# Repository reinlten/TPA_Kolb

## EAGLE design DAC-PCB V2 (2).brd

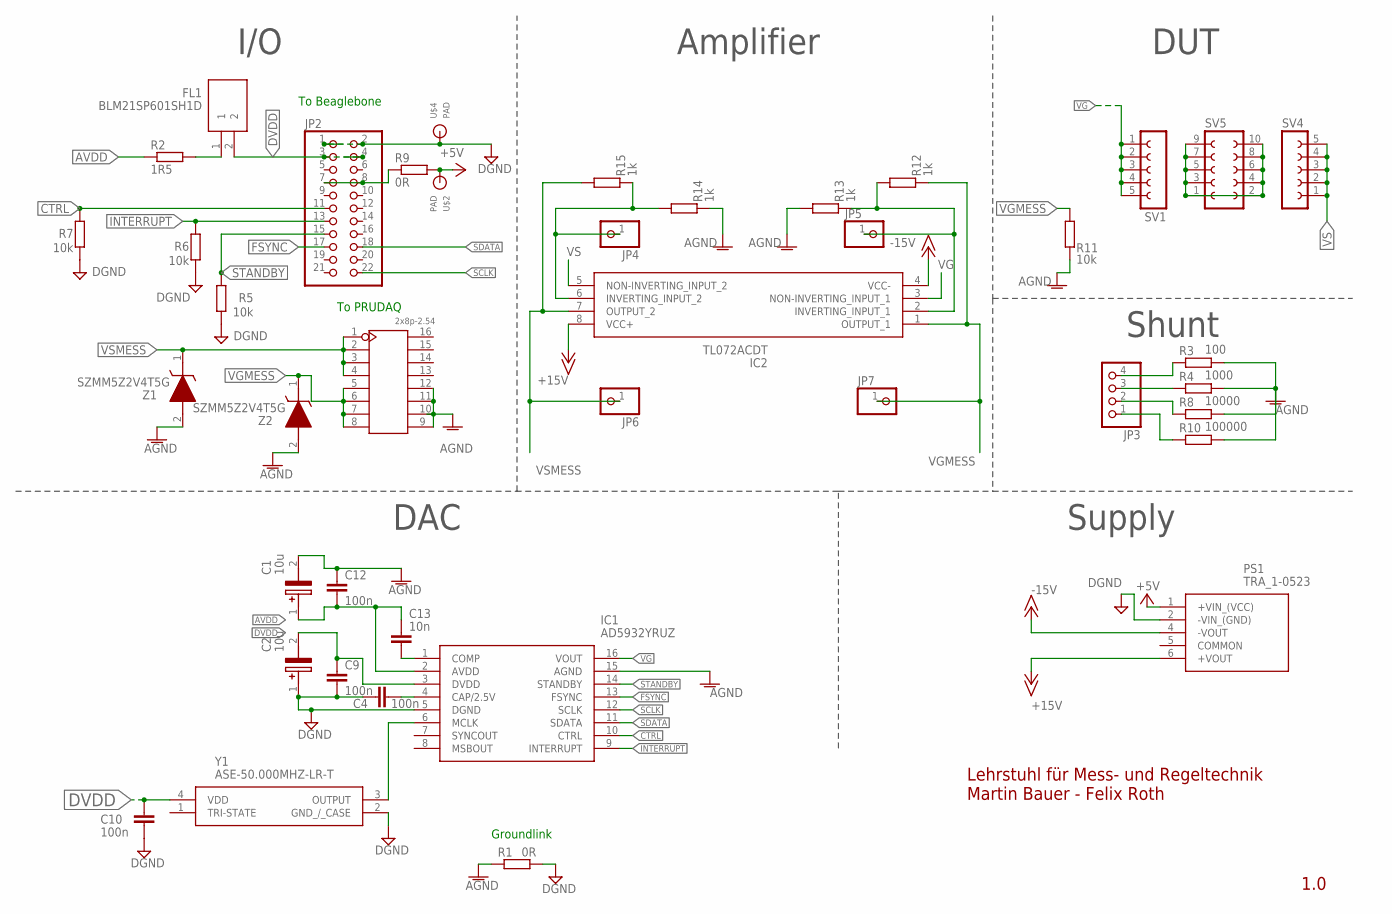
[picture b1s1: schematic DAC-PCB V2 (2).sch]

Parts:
C1, C2: 10u; CAPAE430X550N
C4, C9, C10, C12: 100n; C0805
C13: 10n; C0805
FL1: BLM21SP601SH1D; BLM21AG102BH1J
IC1: AD5932YRUZ; SOP65P640X120-16N
IC2: TL072ACDT; SOIC127P600X175-8N
J2: 2x8p-2.54; H2X8-2.54
JP2: PINHD-2X11; 2X11
JP3: PINHD-1X4; 1X04
JP4, JP5, JP6, JP7: PINHD-1X1; 1X01
PS1: TRA_1-0523; TRA_1-2423
R1: 0R; R1210
R2: 1R5; R0805
R3: 100; R0805
R4: 1000; R0805
R5, R6, R7, R11: 10k; R0805
R8: 10000; R0805
R9: 0R; R0805
R10: 100000; R0805
R12, R13, R14, R15: 1k; R0805
SV1, SV4: FE05-1
SV5: FE05-2
U$2, U$4: PAD; PAD_PROTO
Y1: ASE-50.000MHZ-LR-T; ASE24576MHZLCT
Z1, Z2: SZMM5Z2V4T5G

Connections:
+5V: PS1.1 (+VIN_(VCC)), R9.2, U$2.1
+15V: IC2.8 (VCC+), PS1.6 (+VOUT)
-15V: IC2.4 (VCC-), PS1.4 (-VOUT)
AGND: C1.2 (-), C12.1, IC1.15 (AGND), J2.9, J2.10, J2.11, J2.12, R1.1, R3.2, R4.2, R8.2, R10.2, R11.1, R13.2, R14.1, Z1.2 (A), Z2.2 (A)
AVDD: C1.1 (+), C12.2, C13.1, IC1.2 (AVDD), R2.1
CTRL: IC1.10 (CTRL), JP2.11, R7.2
DGND: C2.1 (+), C4.1, C9.2, C10.2, IC1.5 (DGND), JP2.1, JP2.2, PS1.2 (-VIN_(GND)), R1.2, R5.1, R6.1, R7.1, U$4.1, Y1.2 (GND_/_CASE)
DVDD: C2.2 (-), C9.1, C10.1, FL1.2, IC1.3 (DVDD), JP2.3, JP2.4, Y1.4 (VDD)
FSYNC: IC1.13 (FSYNC), JP2.17
INTERRUPT: IC1.9 (INTERRUPT), JP2.13, R6.2
unnamed: JP3.4, R3.1
unnamed: JP3.3, R4.1
unnamed: C4.2, IC1.4 (CAP/2.5V)
unnamed: FL1.1, R2.2
unnamed: IC1.6 (MCLK), Y1.3 (OUTPUT)
unnamed: IC2.6 (INVERTING_INPUT_2), JP4.1, R14.2, R15.1
unnamed: C13.2, IC1.1 (COMP)
unnamed: JP2.7, JP2.8, R9.1
unnamed: JP3.2, R8.1
unnamed: JP3.1, R10.1
unnamed: IC2.2 (INVERTING_INPUT_1), JP5.1, R12.2, R13.1
unnamed: SV5.1, SV5.2, SV5.3, SV5.4, SV5.5, SV5.6, SV5.7, SV5.8, SV5.9, SV5.10
SCLK: IC1.12 (SCLK), JP2.22
SDATA: IC1.11 (SDATA), JP2.18
STANDBY: IC1.14 (STANDBY), JP2.15, R5.2
VG: IC1.16 (VOUT), IC2.3 (NON-INVERTING_INPUT_1), SV1.1, SV1.2, SV1.3, SV1.4, SV1.5
VGMESS: IC2.1 (OUTPUT_1), J2.5, J2.6, J2.7, J2.8, JP7.1, R11.2, R12.1, Z2.1 (K)
VS: IC2.5 (NON-INVERTING_INPUT_2), SV4.1, SV4.2, SV4.3, SV4.4, SV4.5
VSMESS: IC2.7 (OUTPUT_2), J2.1, J2.2, J2.3, J2.4, JP6.1, R15.2, Z1.1 (K)

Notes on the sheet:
Groundlink
I/O
Supply
DAC
Amplifier
1.0
Lehrstuhl für Mess- und Regeltechnik Martin Bauer - Felix Roth
DUT
Shunt
To Beaglebone
To PRUDAQ

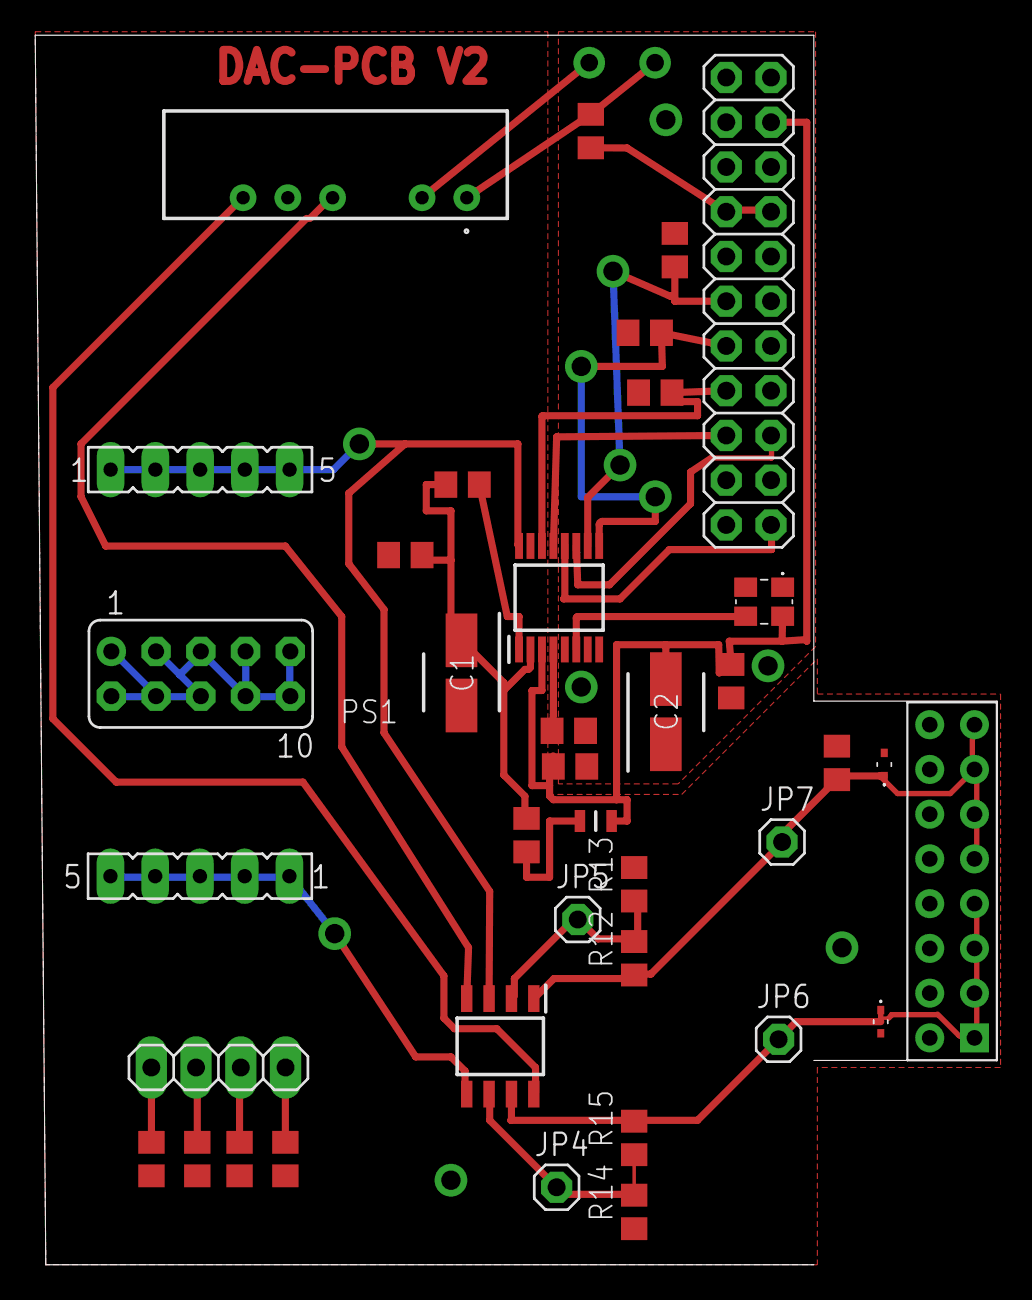
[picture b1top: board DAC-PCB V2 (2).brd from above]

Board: 2 copper layers, 54.6 x 69.8 mm, 41 parts (1 on the bottom side), 29 nets.

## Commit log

2022-12-06 Korr funktioniert noch nicht wirklich und fft mal so gar nicht
2022-12-06 korr geht jetzt, abs hat gefehlt...
2022-12-07 abschnittsweise betrachtung, funktioniert noch nicht
2022-12-07 input file geändert
2022-12-08 Create Auswertung_1
    First iteration of file for basic evaluation
2022-12-15 daten filtern ist wichtig lul
2022-12-18 Messdaten hinzugefügt
2022-12-18 Tiefpass hinzugefügt
2022-12-20 Basic impedance calculator / circuit simulator
2022-12-21 Better visualisation
2022-12-22 Script to evaluate the measurements of the LCR-Meter
2023-01-09 Unbenanntes Diagramm.drawio eingefügt
2023-01-10 Unbenanntes Diagramm.drawio aktualisiert
2023-02-02 zeug
2023-02-03 cleaned version
2023-03-02 better evaluation of one step of bb
2023-03-06 added measurement and signal classes
2023-03-07 simplify and cleaned up the evaluation
2023-03-07 moved evaluation to main method
2023-04-20 moved files
2023-04-20 Komplette 1 kOhm Messung
2023-04-23 added auswertung_oszi
2023-04-23 oszi auswertung funktioniert
2023-04-23 added comments
2023-04-23 some changes and fixes with the dc part
2023-04-28 added compensation for 10 kOhm Resistor (hardcoded value)
2023-04-28 added compensation by factor
2023-05-03 added niquist diagramm and better visualization to evaluation_bbb.py
2023-05-03 added titles to the plots
2023-05-09 added evaluation for one measurement
2023-05-10 Update auswertung_ohne_fft.m
    +nyquist diagramm
2023-05-17 cleaned up and made evaluation better
2023-05-24 cleaner code
2023-05-24 added functionality
2023-05-26 works but has a bug with step100.txt
2023-05-26 fixed bug with wrong index
2023-05-26 program for only evaluating one textfile
2023-06-15 simulation file for real case
2023-06-16 added file for analizing single amplitude diagramm
2023-06-16 added phase diagramm and axis titles
2023-06-22 init
2023-09-09 added new evaluation
2023-09-19 added linus file
2023-09-24 ordered diagramms and cleaned up
2023-10-03 cleaned version and better diagramms
2023-10-06 updated version
2023-10-10 current version
2023-10-11 mit Plot für Frequenzgang U2/U0 und idealem RC Glied
2023-10-11 formatted
2023-10-12 Skript zur Erstellung der Matlab Diagramme
2024-04-12 forschungspraktikum.drawio eingefügt
2024-04-12 forschungspraktikum.drawio aktualisiert
2025-10-22 Masterarbeit.drawio eingefügt
2026-02-22 Masterarbeit.drawio aktualisiert
